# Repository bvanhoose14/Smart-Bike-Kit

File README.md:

# Project BITbike

### Group Members: **Spencer Durrant, Ben Van Hoose, Tristan Stotesbery**

Welcome to our senior project github repository. For information about it please see our [website.](https://bvanhoose14.github.io/Smart-Bike-Kit/)

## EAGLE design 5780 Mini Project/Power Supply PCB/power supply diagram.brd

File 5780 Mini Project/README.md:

# Project BITbike

### Group Members: **Spencer Durrant, Ben Van Hoose, Tristan Stotesbery**

Our idea and goal was to create an **LED matrix** "License Plate" that could be attached to bicycles or ebikes and it could be used to display messages, turn signals or other useful visuals. This LED matrix was controlled by a microcontroller, the **STM32F072B Discovery board**, which was also interfacing with an **ESP32** microcontroller. The purpose of the ESP32 was to facilitate interactions with a **smartphone** utilizing it's **bluetooth** libraries, giving a biker the ability to control an **IoT** system while riding. This mini project also serves as a starting prototype for our broader senior project.

## Functionality/Milestones

The block diagram above shows a high level functionality of the system. We developed an application using Java for the android to work with the bluetooth classic protocol as well as a simple **GUI**. We completed the other end of the bluetooth connection using the ESP32 built in bluetooth module. Then we transferred the information to the STM32 board and handled the incoming **GPIO** signals, interpreting them for the LED matrix. This functionality satisfied our first milestone of the project, to be able to control the MCU with a phone via bluetooth. Below is the GUI displayed on the phone.

The STM32 also served as the controller for the LED matrix and we could display various figures, such as text, or arrows for blinkers. We successfully did this by first using the simpler ESP32 environment to control the LED matrix to understand how to work with it. Then we transitioned to using C with the STM32. Controlling the LED matrix involved writing to it bit-by-bit with precise clocking and following a register address map for the matrix. This took us time to get properly figured out, we utilized **UART** for debugging. We got this working for each MCU demonstrating our success for the second milestone. We also had to use a smaller LED matrix as our STM32 is not fast enough to support the RGB matrix in the image above.

Naturally someone would want all these electrical devices to be powered. So we had to solve our power issue by designing a **power supply PCB** that would safely draw power from a battery pack containing 6 Lithium-Ion battery cells in a 3-Series, 2-Parallel configuration. We first read documents to figure out the maximum power consumption of the two microcontrollers and the LED matrix and we determined the maximum current could potentially reach 4 Amps. The battery and management circuit board we built is rated for 12.6V, 4Ah which is reasonable for our project. Specifically, the PCB would take the battery voltage and use a buck converter IC to drop the voltage to DC 5V. Once we designed, fabricated, and soldered the PCB we plugged it in with our system and it worked as expected. This meant we achieved our third milestone.

We also utilized some of the on-board peripherals of the STM32, specifically the **gyroscope**. As a bike turns it tilts in the direction it is turning. This makes it possible to automatically turn off the blinker signals with the gyroscope. Therefore we used **I2C** to interact with this sensor and turn off the blinker signals once the bike was straightened back out after a turn signal was initiated. This satisfied our goals for our fourth milestone.

# Setup
With several devices on this system, a lot of setup is involved. This requires good detail so as not to mess it up. First, program and flash the ESP32 with the respective code located in one of the two version folders. Then program and flash the STM32 with the respective code in the same version folder. A reference for how the LED matrix works that may be helpful, which we utilized, is [controllers tech](https://controllerstech.com/led-dot-matrix-and-stm32/). 

## Wiring
We have set pins specifically with our designs. See the diagram below to see how to connect the devices together.

Additionally, see the image below for the STM32 pins PB15, PB11, and PB13 for the I2C protocol.

## Schematics
Below is the schematic and PCB layout for the buck converter power supply.

## Power
The assembled power supply is in the image below. All three of the screw terminal connectors are connected to the same 5V line. It is possible to provide power to the board using one of the screw terminals, or the barrel jack. To connect our battery pack to it, we simply connected the wires to one of the screw terminals. For alternative testing it is certainly an option to use a 5V supply with a barrel jack connected to a wall outlet.

To power the microcontrollers and LED matrix, we used one screw terminal for the ESP32, and the other for the STM32 while the third one was occupied with the battery pack. We fed power into the LED matrix from the STM32 5V pin and thus all our devices could be powered for at least an entire hour by the batteries.

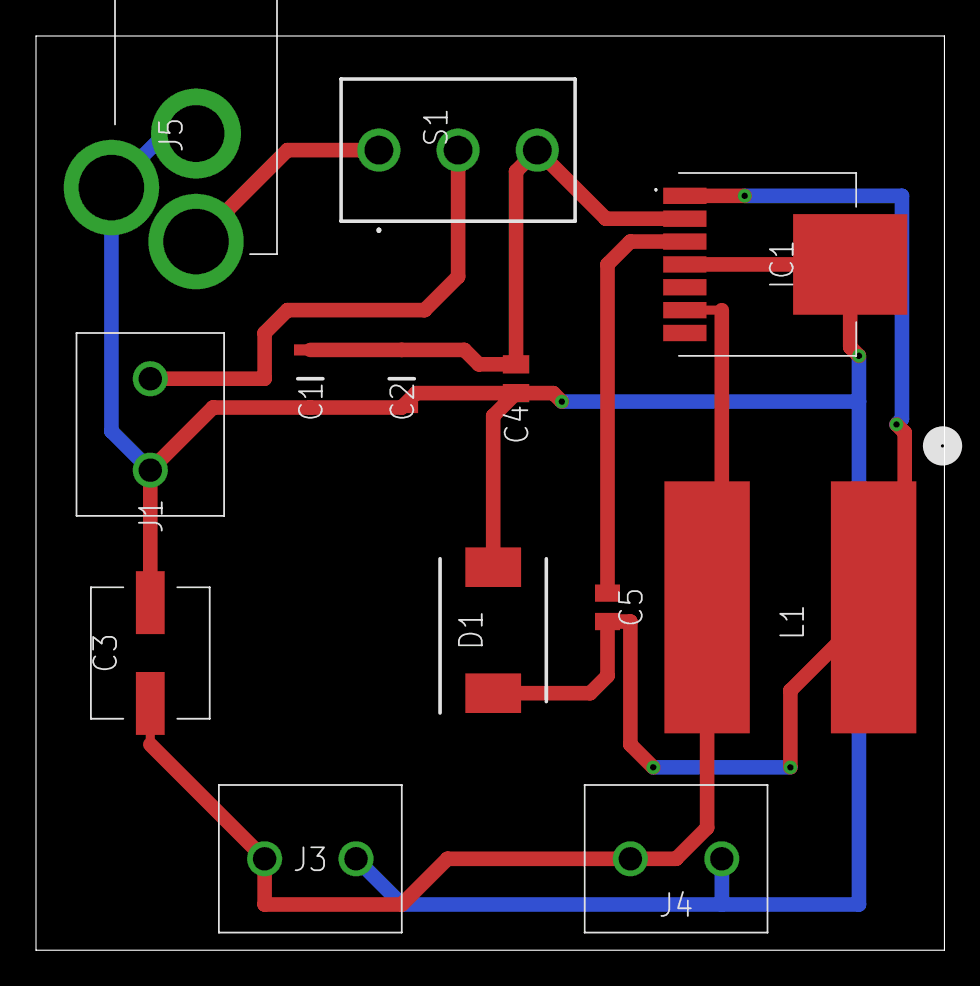
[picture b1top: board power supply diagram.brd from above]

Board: 2 copper layers, 50.5 x 50.8 mm, 13 parts (0 on the bottom side), 7 nets.

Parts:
C1, C2: C3216X6S1V106K160AC; CAPC3216X180N
C3: 16SVPE180M
C4: C0805C105K4RACTU; CAPC2012X100N
C5: CC0805KRX7R9BB103; CAPC2012X135N
D1: B540C-13-F; DIOM7959X250N
IC1: LM22678TJ-5.0_NOPB; LM22678TJ50NOPB
J1, J3, J4: TB006-508-02BE; TB00650802BE
J5: CON-SOCJ-2155; CONSOCJ2155
L1: SDR1307-4R7ML; SDR1307-220ML
S1: 8SS1022-Z; 8SS1022Z

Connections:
GND: C1.1, C2.1, C3.2, C4.1, D1.2, IC1.4, IC1.8, J1.1, J3.2, J4.2, J5.2, J5.3
unnamed: C1.2, C2.2, C4.2, IC1.2, S1.3
unnamed: J1.2, S1.2
unnamed: C5.1, IC1.3
unnamed: C5.2, D1.1, IC1.1, L1.1
unnamed: C3.1, IC1.6, J3.1, J4.1, L1.2
unnamed: J5.1, S1.1

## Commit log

2021-03-19 set up
2021-03-19 resources/note page added
2021-03-24 pic adjust
2021-04-02 added block diagram
2021-04-03 updated notes, just go with VSCode
2021-04-14 not working yet
2021-04-18 BITbike
2021-04-19 Updated timeline
2021-04-29 Matrix with STM32 first working version
2021-04-30 Added Turn Signal, Cancelling, and App code
2021-04-30 Power Supply Schematic and PCB Layout
2021-05-02 adding diagram
2021-05-02 update diagram
2021-05-02 power supply pdfs
2021-05-02 makin readme
2021-05-02 figuring images out
2021-05-02 moar readme
2021-05-02 Final edit
2021-05-02 Remove LED SCROLLING
2021-05-02 added LED_off function
2021-05-03 Organized Files for 5780 Project
    Seperated code into 2 versions: V1 is the code that has self-cancelling turn signals working
    V2 is the code that is running the LED Matrix off of the STM32 instead of the ESP32
2021-05-04 mini project complete
2021-05-04 picture update
2021-05-04 hopefully final readme update
2021-05-04 final readme update, all typos and grammar fixed
2021-08-07 Uploading Android App stuff to Github
    app on github
2021-08-07 filenames
2021-08-08 bikestuff fix
    fixing bikestuff
2021-08-09 Updated Maps
    Maps now track user location
2021-08-12 Implementing Bluetooth
    Starting to combine bluetooth functionality with the map api
2021-10-20 rgb-led
2021-10-20 gyro logger
2021-10-20 Added Block diagram to resource folder
2021-10-20 Added my sensor files
2021-10-20 pin update
2021-10-20 rename folder
2021-10-21 fixed the distance sensor bug
2021-11-10 matrix-turn signal sys update
2021-11-11 first 3d print file
2021-11-15 Updates to my code
